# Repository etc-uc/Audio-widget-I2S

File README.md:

# Audio-widget-I2S
**Interfata audio USB utilizand un AVR32 pe protocolul I2S**

## Introducere
>
>Inca din timpurile dinaintea erei digitale, consumatorii de audio **asa zisii audiofili** au fost in cautare de metode pentru reducerea la minim a distorsiunilor transmise catre difuzoare,si implicit,percepute de urechea umana.In vremea respectiva,data fiind si complexitatea destul de redusa a dispozitivelor,ideea reducerii distorsiunilor in sisteme era destul de limitata de topologiile propuse,de aceea aparitia sistemelor digitale de procesare in audio a dus la reducerea drastica a neajunsurilor semnalelor analogice.Pentru **puristi** , circuitele digitale si DSP-urile sunt considerate _un sacrilegiu_ adus audiofiliei,dar este unul justificat,deoarece in ciuda complexitatii mai ridicate fata de un circuit analog pur , sistemele digitale sunt mult mai eficiente fata de complementele sale,iar posibilitatea customizarii lor este foarte mare (spre deosebire de un circuit analogic unde,pentru a modifica o caracteristica trebuie regandit tot circuitul,in cazul unui circuit digital cu uC este doar o problema de software).

>Aparitia interfetelor audio s-a facut odata cu dezvoltarea PC-urilor si inregistrarea de muzica/sunete pe medii digitale , in pofida benzilor magnetice si a discurilor de vinil , deoarece era necesara o metoda de redare a sunetelor stocate pe calculatoarele vremii. De altfel,primele asa zise **placi de sunet** si-au facut aparitia prin calculatoare in jurul generatiei 80486 , cand deja exista o oarecare structura de operare stabila pe 16 biti , iar pentru o esantionare simpla a sunetelor erau arhisuficiente instructiunile implementate de Intel in procesoarele respective.
>>_Daca facem referinta la vremurile actuale,se poate spune ca practic nici nu se punea problema de calitate sau termenul de **Hi-Fi** in acele vremuri,dar acele sunete au reprezentat ceea ce urma sa fie boom-ul erei digitale_
>
>Ca si istorie a acestei ere in care traim,se pot scrie foarte multe lucruri deja cunoscute,asa ca voi incerca sa ma concentrez pe esential.

>Ideea de "calitate audio" pe digital a aparut in momentul lansarii pe piata mondiala a CD-ului (acel lucru care acum multora dintre noi ni se pare atat de outdated,ori chiar nu il mai folosim),dar el a avut cea mai mare influenta in aparitia de tehnologii de compresie si codare audio.Ca si concept,ideea de CD a aparut prin anul 1980 ,cand Philips si Sony au incheiat un parteneriat de cercetare in domeniul digital,dorindu-se un mediu de stocare unic transmisibil,care sa aibe un spatiu de stocare a informatiilor mult mai mare decat cel al dischetelor "floppy" si al benzilor magnetice,dar totusi sa nu coste cat un hard disk al vremurilor (memo: un hard disk de tip Winchester avea o capacitate de maxim 128MB , cantarea in jur de 15-20kg si era cam cat un desktop SFF actual ca dimensiuni si costa in jur de ~5.000 de dolari unul?).
>>Standardul CD a fost definitivat in jurul anului 1983,iar in urma intelegerii realizate intre cele 2 concerne se va realiza trecerea industriei audio catre acest mediu.

>Se pune problema "compresiei audio".In a nutshell,algoritmul de compresie audio se refera la un standard de scriere-redare a sunetelor pe calculatoare. Calculatoarele,la momentul respectiv avand sisteme de operare stabile precum UNIX si DOS (vorbind de anii '80,dar regula se aplica si in prezent pe sistemele actuale),pentru a reda sunetele stocate pe medii precum hard-diskul se folosesc de niste software numite **codec** .
>>Codecurile,in esenta,sunt niste pseudo-drivere pe care sistemul de operare le interpreteaza atunci cand se executa in sistem un fisier cu extensia ce corespunde codecului respectiv.
>>Adica,spre exemplu, avem un fisier cu extensia ".mp3" , SO va sti ca la instantierea acestui fisier va trebui sa apeleze un Codec LAME(Lame Ain't an MP3 Encoder - care este o derivatie imbunatatita de-a lungul anilor de diversi programatori din conceptul original gandit de institutul Fraunhofer din Germania).

>De altfel , toate procedeele de redare/compresie si extensiile de sistem au fost posibile datorita codarii PCM (Pulse Code Modulation).
PCM reprezinta transformarea semnalelor analogice in semnale digitale printr-un algoritm de esantionare constanta a amplitudinii semnalului analogic ,iar fiecare esantion este cuantizat la cea mai apropiata valoare dintr-o gama de cuante apropiate.
>>**Codarea PCM prezinta 2 proprietati ce determina calitatea conversiei semnalului original raportat la acesta : rata de esantionare a semnalului si _bit depth_,care reprezinta cantitatea de biti al fiecarui esantion realizat (un CD-Audio prezinta un bit depth de 16 biti per esantion , pe cand un Blu-ray sau DVD-Audio 24 de biti per esantion).**
>>> Extensiile posibile unei compresii PCM sunt ".wav" ,".L16",".PCM",".AIFF",".AU"

>Pe baza codarii/compresiei PCM a fisierelor audio, cei de la Philips au realizat in anul 1986 (si ulterior revizuit in 1996) un protocol de transmisie seriala al datelor audio intre dispozitive / circuite integrate , protocol care inca se foloseste cu succes si in prezent in dispozitivele audio. Este cunoscut sub acronimul I2S sau IIS **Inter-IC Sound** si se bazeaza pe o magistrala sincrona de transmisie de date (clockul de transmisie intre circuite este separat de magistrala de date,deci implicit receptorul nu mai are nevoie de un circuit suplimentar de refacere a frontului de ceas trimis de emitator).
>Protocolul este relativ usor de interpretat, in principal avem de-a face cu 3 semnale : bit clock line(**BCLK**) , word clock line (cunoscut sub denumirea oficiala de 'word select' **WS** sau 'left-right clock' **LRCLK** ) si cel putin o linie de date multiplexata **SD**

>>Adeseori se mai poate intalni peste cele 3 semnale cunoscute inca un semnal de tact (care nu face parte din protocol) cu rolul de a sincroniza operatiile interne ale DAC-urilor cu cele ale controllerului . Este gasit sub acronimul de "Master clock" **MCLK**
>>>Frecventa tipica de lucru se calculeaza dupa formula : **MCLK = 256 * LRCLK**

###### Cum functioneaza protocolul:

>Semnalul de "Word Select" permite dispozitivului receptor sa 'vada' ce canal urmeaza sa fie trimis , deoarece I2S permite ca pe aceeasi linie de date sa fie trimise 2 canale,fiind un semnal cu factor de umplere 50% si frecventa egala cu cea de esantionare a semnalului trimis.
>>**Pentru semnale stereo , in brosura de specificatii a I2S se spune ca semnalul audio de pe canalul stang se transmite pe palierul de 0 al Word Select , iar canalul drept pe palierul de 1 . De obicei , semnalul "Word Select" este sincronizat dupa fronturile cazatoare ale semnalului BCLK , deoarece datele sunt zavorate pe fronturile crescatoare**.
>>
>Se stabileste semnul liniei de date si se codeaza in complement fata de 2 cu primul bit MSB-ul . **Acest lucru permite ca numarul de biti per cadru sa fie arbitrar , fara a fi nevoie de "negociere" intre emitator si receptor **.

## Specificatii montaj:

1.
 a)Microcontroller utilizat:  Atmel AT32UC3A3256 
 >>>  A complete system-on-chip 32-bit AVR microcontroller. It is designed for cost-sensitive embedded applications that require low power consumption, high code density and high performance.

 >>> The microcontroller's Memory Protection Unit (MPU) and fast, flexible interrupt controller support the latest real-time operating systems. Higher computation capabilities are achievable using a rich set of DSP instructions. The device incorporates on-chip flash and SRAM memories for secure and fast access. 64 KBytes of SRAM are directly coupled to the 32-bit AVR UC3 for performance optimization. Two blocks of 32 Kbytes SRAM are independently attached to the high speed bus matrix for real ping-pong management.

 >>> The microcontroller achieves exceptionally high data throughput by combining the multi-layered 32-bit AVR databus,128 KB on-chip SRAM with triple high speed interfaces, multi-channel peripheral, memory-to-memory DMA controller, high-speed USB embedded host, SD/SDIO card, MLC NAND flash with ECC, and SDRAM interfaces.

 >>> This device features 256KB internal high-speed flash and full-duplex multi-channel I2S audio interface.
 
 b) DAC utilizat: PCM5102A

 >>>The PCM510xA devices are a family of monolithic CMOS-integrated circuits that include a stereo digital-to-analog converter and additional support circuitry in a small TSSOP package. The PCM510xA devices use the latest generation of TI’s advanced segment-DAC architecture to achieve excellent dynamic performance and improved tolerance to clock jitter.

 c) Amplificator/buffer iesire folosit : TPA6120
 >>>In applications requiring a high-power output, very high fidelity headphone amplifier, the TPA6120A2 replaces a costly discrete design and allows music, not the amplifier, to be heard. The TPA6120A2’s current-feedback AB amplifier architecture delivers high bandwidth, extremely low noise, and up to 128dB of dynamic range.
 
2.Utilizeaza USB Audio Class 1 / 2.

3.Capabilitati de redare audio pana la 24bit/96kHz (bit depth / sampling rate).

4.Tensiune de alimentare: 5V (doar daca utilizam DAC-ul si interfata I2S) , +12/-12V (daca se utilizeaza si amplificatorul final)

5.Consum max: 1-1,5A (este necesara alimentare suplimentara deoarece amplificatorul final de casti se alimenteaza diferential) 

### Constructie montaj:

Contructia se bazeaza pe un design modular , iar in acest sens voi concepe intregul sistem pe 4 placi:
 - una o va constitui interfata emulatoare usb-i2s
 - o placa pentru DAC si , eventual , buffere de iesire
 - o placa pentru amplificatorul final
 - o placa pentru alimentare suplimentara

Ideea conceperii montajului intr-un sistem modular este pentru imbunatatirea "lantului" pe decursul timpului (ex. realizarea unui DAC mai performant din perspectiva SNR / PSRR sau schimbarea unei surse liniare cu una in comutatie sau adaugarea de acumulatori pentru portabilitate etc.)

De altfel,un montaj modular poate presupune o asezare mai buna in cutie si,totodata, un ecranaj mai bun al partilor **mai sensibile** fata de circuitul de alimentare.

#### Particularitate software:

Ideea interfetei I2S este bazata pe un proiect deja existent in mediul online , anume SDR-Widget https://github.com/borgestrand/sdr-widget

Asadar hardware-ul din spatele acestui sistem a fost dezvoltat in asa fel incat firmware-ul cu care am programat AVR-ul sa fie direct compatibil.
Din punct de vedere functional, din software-ul dezvoltat in acel proiect am folosit doar mediul de comunicare audio via USB (UAC1 si UAC2) si partea de control software a volumului.

Consider ca nu este necesar sa uploadez toate sursele C pentru generarea firmware-ului , asa ca voi atasa fisierul HEX(.elf) continand versiunea stabila de firmware pentru acest sistem.

#### Programarea microcontrollerului:

Seria UC3A3 de la Atmel(Microchip-ish or whatsoever) au incarcate din fabricatie un bootloader ce contine un USB DFU(Device Firmware Upgrade).
DFU este un protocol ce se regaseste in orice tip de terminal ce are propriul sistem de operare,deoarece faciliteaza operatiunea de rescriere a software-ului deja setat in terminalul respectiv utilizand o interfata de comunicare uzuala.

De aceea , microcontrolerul pe care l-am utilizat in montaj (AT32UC3A3256) l-am programat cu doar un USB si programul ATMEL FLIP 3.4.7 , utilizand din acesta batchisp-ul (pentru ca,prin constructia sa , programul Flip nu suporta la un nivel stabil aceasta serie de uC-uri).

Nu mai pot reproduce inca o data procesul de programare (sau il voi mai face ulterior daca dezvolt un alt firmware mai performant pentru cerinta data), dar comanda de programare pe care am utilizat-o este:
**batchisp -device at32uc3a3256 -hardware usb -operation erase f memory flash blankcheck loadbuffer widget.elf program verify start reset 0**
Unde widget.elf se inlocuieste cu denumirea HEX-ului de urcat pe uC.

Dupa introducerea comenzii se executa programarea uC-ului in 11 pasi:

AT32UC3A3256 - USB - USB/DFU

Device selection....................... PASS

Hardware selection..................... PASS

Opening port........................... PASS

Reading Bootloader version............. PASS    1.0.3

Erasing................................ PASS

Selecting FLASH........................ PASS

Blank checking......................... PASS    0x00000 0x3ffff

Parsing ELF file....................... PASS    widget.elf

WARNING: The user program and the bootloader overlap!

Programming memory..................... PASS    0x00000 0x1c43f

Verifying memory....................... PASS    0x00000 0x1c43f

Starting Application................... PASS    RESET   0

Summary:  Total 11   Passed 11   Failed 0

Dupa programarea uC-ului calculatorul "teoretic" ar trebui sa il recunoasca automat si sa instantieze driverul necesar utilizarii acestuia. Cel putin in Windows 10 nu exista probleme de compatibilitate a driverelor, recunoscandu-le automat la conectarea interfetei. Posibil sa existe probleme de "backwards compatibility" a firmware-ului cu versiunile mai vechi de Windows,dar se rezolva instaland manual "inf drivers".

## Utilizare:

Ca si software , interfata este gandita destul de simplist,deoarece se considera ca este suficient doar un control al volumului,niciun fel de egalizare grafica sau corectie de tonuri.
Software-ul de control este scris pe framework-ul ASIO (_Audio Stream Input-Output_).
Ca si un mic memo : ASIO este un protocol de drivere open-sourced pentru "sound card-uri" specificat in industria audio de firma Steinberg.
Ca si functionare a protocolului : ASIO produce un bypass al caii audio normale la nivel de aplicatie din sistemul de operare utilizat,astfel incat sa se evite "layer-ele" suplimentare la nivel de software.Acest lucru permite aplicatiei sa se conecteze la sound card direct,fara intermedierea sistemului de operare in procesul respectiv.Acest lucru duce la o reducere foarte mare a latentei de transfer a informatiei audio de la soft la hard.

>>Foobar2000 **logo de mai sus** este un player audio freeware (nu este necesara licenta de utilizare) pentru Microsoft Windows, iOS, si Android dezvoltat de Peter Pawłowski.Ca si software este cunoscut designul sau extrem de modular , multitudinea de caracteristici si flexibilitatea in configurare pentru user.
>>Acest player suporta foarte multe formaturi audio , prezinta o multitudine de caracteristici organizarea fisierelor , metadata si are implementata o interfata de convertor utilizabila in linie de comanda (transcodare fisiere si ripping CD-Audio). 

In poza , aplicatia redand un fisier audio .FLAC (lossless audio codec) , configurat pentru output pe WASAPI* , buffer length minim pentru jitter scazut intre interfata de comunicare si controller.

>>>> **Ca si ASIO , WASAPI (Windows Audio Session API) este un plugin utilizat in audio pentru a permite trecerea fluxului de date audio direct intre terminalul audio din aplicatia ce reda fisierele audio**
>>>> Diferenta principala dintre ASIO si WASAPI este ca , primul este un plugin open-source (poate fi luat si modificat in drivere de oricine) , pe cand cel din urma este conceput de MICROSOFT si na...copyright in a nutshell daca vrea cineva sa modifice core-ul plugin-ului.

>>>Ca si comparatie intre cele 2 pluginuri, ambele sunt foarte usor de utilizat si instalat , cu precizarea ca ASIO functioneaza cu doar cu dispozitivele ce au descriptori dedicati in driverele lor , pe cand WASAPI functioneaza cu orice fel de endpoint device , atata timp cat este selectat pluginul ca si output pentru device-ul respectiv si nu adresa "Direct Sound".

>>>> **De precizat ar mai fi ca,atata timp cat un eveniment WASAPI / ASIO este executat , nu se mai reda niciun flow audio din partea altor aplicatii pana nu se incheie evenimentul respectiv**

### Ansamblare

Pentru incapsularea proiectului am ales sa separ sursa de alimentare de partea de DAC+Amplif casca pentru a evita producerea de zgomot inutil in sistem. **ideea este tocmai de a avea un zgomot minim in tot lantul si atunci este de preferat ca sursa sa stea cat mai departe de elementele sensibile ale sistemului**

Asadar , pentru incapsularea amplificatorului am comandat o carcasa din aluminiu eloxat argintiu de la Hammond,cu dimensiunile 220x103x31mm (LxlxH) , iar pentru sursa probabil voi utiliza o cutie de ramificatie electrica **de aparataj** pentru ca nu are prea mare importanta aspectul ei (ca oricare alta sursa de alimentare, va sta intr-un loc prea putin vizibil).

Pentru alimentare voi monta pe ambele carcase o mufa DIN 3P ce se asigura cu o piulita de blocare , cu 3 pini deoarece amplificatorul se alimenteaza diferential.

#### Masuri pentru evitarea producerii/captarii de zgomot in circuit:

1.Decuplarea alimentarilor cu condensatoare de valoare foarte mica (capabilitate de lucru in frecvente mari) - zeci/sute nF si de valoare f. mare (capabilitate de lucru in frcvente mici).

2.Torsadarea cablurilor de alimentare din carcasa (reducerea emisiilor em. in circuit).

3.Separarea pe cat posibil a circuitelor de semnal mic fata de cele de alimentare.

4.Utilizarea unui punct comun de legatura a maselor din intregul circuit (star pattern sau line pattern , in cazul meu voi utiliza un line pattern deoarece nu sunt implicati curenti mari de circuit - max 1A peak).

5.Utilizare de filtraj cat mai generos - capacitatile mari de filtrare implica un riplu foarte mic al sursei de alimentare,deci posibilitatea aparitiei unui zgomot perturbator pe alimentare minim.
>>Cu riscul aparitiei unui curent de incarcare foarte mare,se recomanda utilizarea de capacitati mari pentru evitarea riplului,mai ales in circuite unde este nevoie de curenti mari pe perioade scurte.
>>>Problema curentilor mari de incarcare se rezolva cu niste rezistente serie cu condensatorii (zeci de ohmi),care sa limiteze curentul prin ei la pornire,dupa aceea rezistentele se sunteaza cu un releu si se utilizeaza normal **soft-start empiric**

**RIPLU -> componenta alternativa aparuta la ciclurile de incarcare-descarcare ale condensatorilor intr-un redresor**

## Limitari si probleme aparute de-a lungul constructiei:

Cea mai mare problema am avut-o la ansamblare...un cosmar si jumatate din perspectiva unei persoane ce a lucrat mai tot timpul cu componente THT si acum s-a lovit de "zidul" lipirii de componente SMD. Am facut si prostia de a ma apuca si fix de cea mai complicata placa mai intai , cea a interfetei USB-I2S, cei 144 de pini ai uC-ului mi-au dat de furca pana l-am lipit cum trebuie,deoarece m-am incapatanat sa il lipesc pin cu pin cu letconul si la un moment dat aveam efectiv mai multe scurturi intre pini decat pini lipiti cum trebuie de placa.Dar acest mic detaliu a fost rezolvat cu mult flux,efect capilar si injuraturi cand nu voia fludorul sa plece dintre pini pe talpa varfului folosit.
De altfel ,toate componentele 0603 de pe aceasta placa mi-au provocat o mare placere de a invoca sfinti de-a lungul lipirii lor.
Apexul a fost atins la ora 3 noaptea,dupa ce am terminat de lipit placuta interfetei,am legat-o la USB si am realizat,cu stupoare,ca nu face nimic...nu se conecta la calculator.Din nou,nervi injuraturi,abtineri din a tranti minunea peste tot.
A doua zi am rezolvat problema in 10 minute : stabilizatorul 5V-3.3V de pe placa avea un pin " in aer " si nu aveam output pentru alimentarea uC-ului.

**Morala ar fi ca: prea multe beri si oboseala dupa 12 ore de alergat dintr-o parte in alta dauneaza bunei atentii asupra realizarii unui montaj.**

Montarea placii DAC a fost pretty straightforward , nu am intampinat cine stie ce dificultati, mai ales acum avand experienta lipirii "ghindoacelor" 0603 pe placa interfetei ... componentele 1206 si integratul SSOP cu 20 de pini au fost PARFUM!!

Placa amplificatorului am montat-o si cam atat, pana acum m-am folosit doar de mufa de casca pentru a vedea daca functioneaza dacul cum trebuie.Urmeaza sa montez si sursa de alimentare si o voi testa si pe aceasta.

Singura limitare "constructiva" mi-am creat-o singur,din pricina carcasei alese pentru circuit. Am ales o carcasa cu inaltimea de 31mm, insuficient pentru inaltimea potentiometrului pe PCB-ul amplificatorului.Am fAacut aceasta eroare deoarece nu am tinut cont ca primele caneluri de suport pentru cablaje incep de la aproximativ 5mm fata de fundul carcasei , ceea ce ar insemna ca depasesc inaltimea montarii capacului cu potentiometrul cu vreo 2mm din ce am masurat.

Solutia: montat potentiometrul si mufa de casca solitare pe panoul frontal si facut legaturi cu PCB-ul prin cabluri torsadate si mufate.

## Constructie sursa de alimentare

Cel mai mare semn de intrebare posibil din tot proiectul ce se putea pune : Ce sursa de alimentare sa folosesc , liniar sau comutatie? Cum naiba fac sa nu stric tot "zenul" montajului cu zgomote inutile aduse de catre o sursa?

De altfel, orice sursa as alege inevitabil tot ma aleg cu un oarecare zgomot in circuit,pentru ca nu poti elimina o cauza fara a genera un alt defect.

Solutia : **in mintea mea** 

Se da o sursa clasica stabilizata , realizata extern circuitelor de semnal / amplificat. Sursa o voi realiza cu un transformator incapsulat in rasina de 10-15VA,deoarece nu am nevoie de foarte multa putere de iesire. Redresare cu punte de diode clasise / schottky (inca nu m-am decis daca se merita efortul pentru diode schottky,mai ales pentru frecventa retelei).

Filtraj inainte de stabilizare 2x4700uF + decuplarile de rigoare pe diode cu 100nF + 220-470nF in bratul stabilizatorului + buffer suplimentar de curent dupa stabilizatoare 2x4700uF + 100nF. Bufferul il voi amplasa in carcasa interfetei,pentru a realiza si punctul comun de legatura al masei pentru tot circuitul.

Imi asum riscul ca voi avea un curent initial de incarcare enorm pentru acel transformator (10000uF insumati pot produce un oarecare deranj mai ales pentru o sursa ce nu debiteaza un curent foarte mare),dar acest lucru il voi vedea exact cand voi finaliza si acest pas.

Stabilizatoarele probabil vor fi clasicele 7812/7912 (not so many fancy things there , sursa trebuie sa fie cat mai simpla si eficienta,fara prea multe briz-briz-uri).

## Final updates

1. La indemnul tatalui meu am achizitionat inca o carcasa de la Hammond , "sora" celei pe care am prezentat-o mai sus , din pricina incapsularii tuturor modulelor intr-un singur loc si nu "in o mie si una de cutiute". Ca si forma sunt identice,singura diferenta o face inaltimea lor (31mm vs 53mm).

2. Am ansamblat sursa de alimentare *dupa lupte seculare as putea spune* si am descoperit ca pentru ce am eu nevoie 4700uF pe brat de alimentare este mai mult decat suficient.Dupa cum ma asteptam , folosind pattern-ul line pentru legarea maselor la comun si decuplarea "sanatoasa" a elementelor sursa nu induce zgomot in circuite...great succes i would say :)
Singura problema: am facut-o pe cablaj de test pentru ca nu am mai avut rabdare sa corodez o foaie de cablaj ... but not so much of a thing pentru ca am tinut cont de dimensionarea corecta a traseelor de circuit si pozitionarea elementelor disipatoare de caldura astfel incat circuitul sa nu se degradeze rapid,dar totusi sa fie compact si sa se incadreze in aria necesara.

3. Odata cu sursa,am testat intr-un final si amplificatorul final si pot spune ca a meritat asteptarea...chiar suna foarte bine in combinatie cu dacul facut.Imi era foarte teama de imperecherea lor,dar a fost doar paranoia si atat.

Dar credeti ca am scapat de peripetii? Nicio sansa, la prima "cheie" amplificatorul nu a vrut sa cante nici sa-l fi batut.
Am incercat sa elimin toate posibilele cauze , in prima instanta am inlocuit toate cablurile de legatura dar degeaba ca tot nu a vrut sa mearga. Am sucit sursa pe toate partile,am zis ca poate am legat ceva prost pe acolo,dar nicio sansa,toate legaturile erau facute bine si aveam tensiune aproape egala pe ambele brate de alimentare.Ce mama masii sa mai aiba si placa asta acum?!
Am legat dacul direct la iesirea de casti si aveam semnal redat,deci nicio sansa sa fie din alta parte problema.
Deschid schema , stau si ma uit la layoutul cablajului si dupa realizez ca integratul meu amplificator este montat invers pe pcb ... #$%^#$$@$^$%^#$#@%#$^ masii de treaba. Tuff job de dezlipit din cauza fludorului ce tine padul de disipatie termica lipit de cablaj.Din nou,sfinti,altare si tot tacamul pana l-am dezlipit si relipit (noroc cu colegul de camera muuuultt mai rabdator decat mine).
Dupa ce l-am relipit zeii siliciului au decis sa nu imi arda integratul si l-am putut auzi cantand, finally . Intr-un final , tot lantul meu audio este gata si functional, iar singurul lucru ce mi-a mai ramas de facut este sa gauresc panoul frontal si sa strang ultimele 4 suruburi de pe cutie :)

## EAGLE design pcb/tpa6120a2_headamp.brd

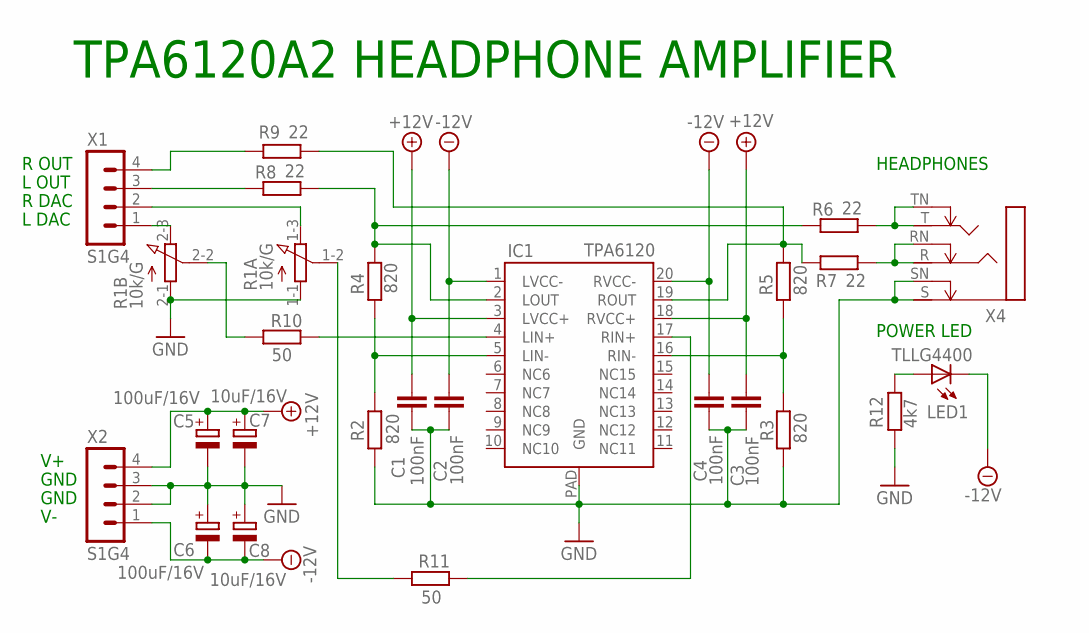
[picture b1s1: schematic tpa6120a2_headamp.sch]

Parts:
C1, C2, C3, C4: 100nF; C1206
C5, C6: 100uF/16V; SMC_D
C7, C8: 10uF/16V; SMC_C
IC1: TPA6120; SO20POWERPAD
LED1: TLLG4400; LED3MM
R1: 10k/G; ALPS-RK27-DUAL
R2, R3, R4, R5: 820; R1206
R6, R7, R8, R9: 22; R1206
R10, R11: 50; R1206
R12: 4k7; R1206
X1, X2: S1G4; MA04-1
X4: NMJ6HCD2

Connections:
+12V: C1.1, C3.1, C5.+, C7.+, IC1.3 (LVCC+), IC1.18 (RVCC+), X2.4
-12V: C2.1, C4.1, C6.-, C8.-, IC1.1 (LVCC-), IC1.20 (RVCC-), LED1.K (C), X2.1
GND: C1.2, C2.2, C3.2, C4.2, C5.-, C6.+, C7.-, C8.+, IC1.PAD (GND), R1.1-1 (1), R1.2-1 (1), R2.1, R3.1, R12.1, X2.2, X2.3, X4.S, X4.SN
unnamed: IC1.19 (ROUT), R5.2, R7.1, R9.2
unnamed: IC1.5 (LIN-), R2.2, R4.1
unnamed: IC1.16 (RIN-), R3.2, R5.1
unnamed: IC1.2 (LOUT), R4.2, R6.1, R8.2
unnamed: R6.2, X4.T, X4.TN
unnamed: R1.2-3 (3), X1.1
unnamed: R1.1-3 (3), X1.2
unnamed: R1.2-2 (2), R10.1
unnamed: R1.1-2 (2), R11.1
unnamed: R7.2, X4.R, X4.RN
unnamed: IC1.4 (LIN+), R10.2
unnamed: IC1.17 (RIN+), R11.2
unnamed: LED1.A, R12.2
unnamed: R8.1, X1.3
unnamed: R9.1, X1.4

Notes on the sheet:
TPA6120A2 HEADPHONE AMPLIFIER
L DAC
R DAC
L OUT
R OUT
GND
HEADPHONES
POWER LED

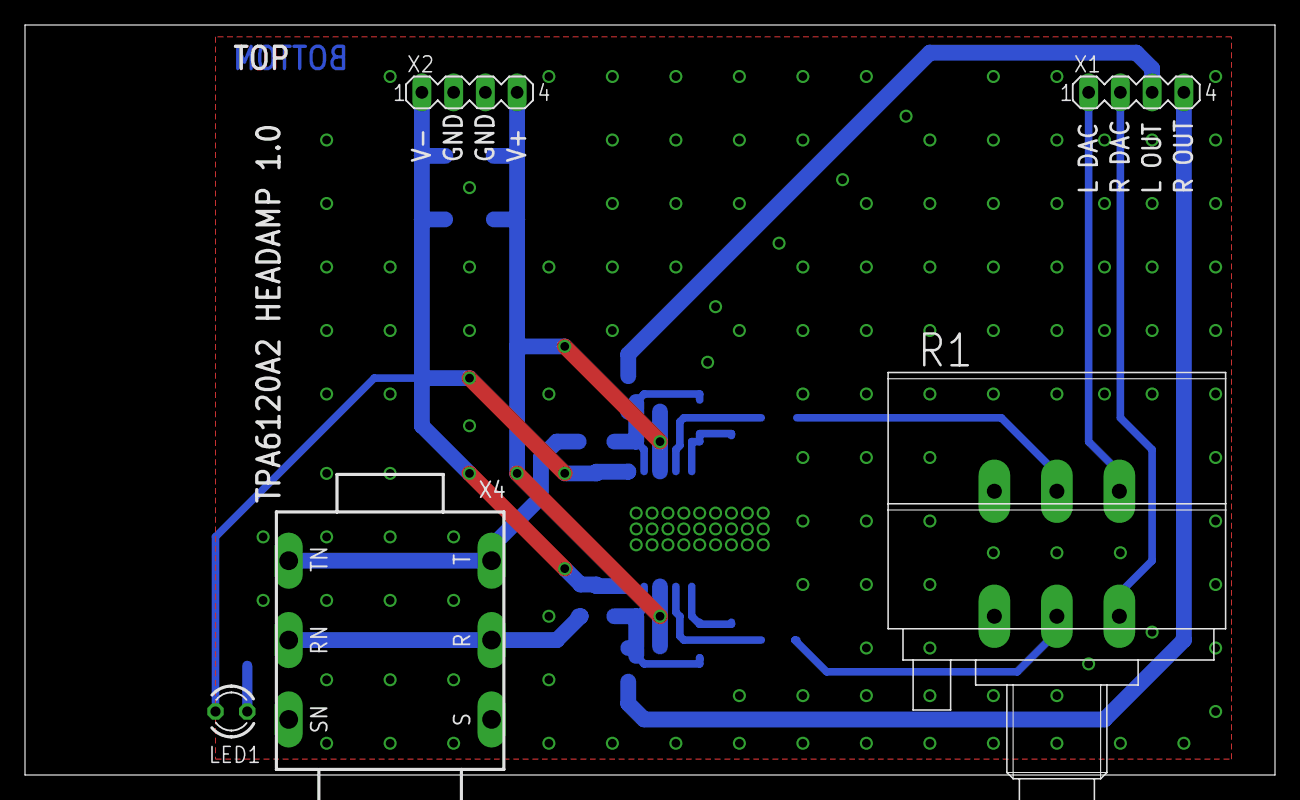
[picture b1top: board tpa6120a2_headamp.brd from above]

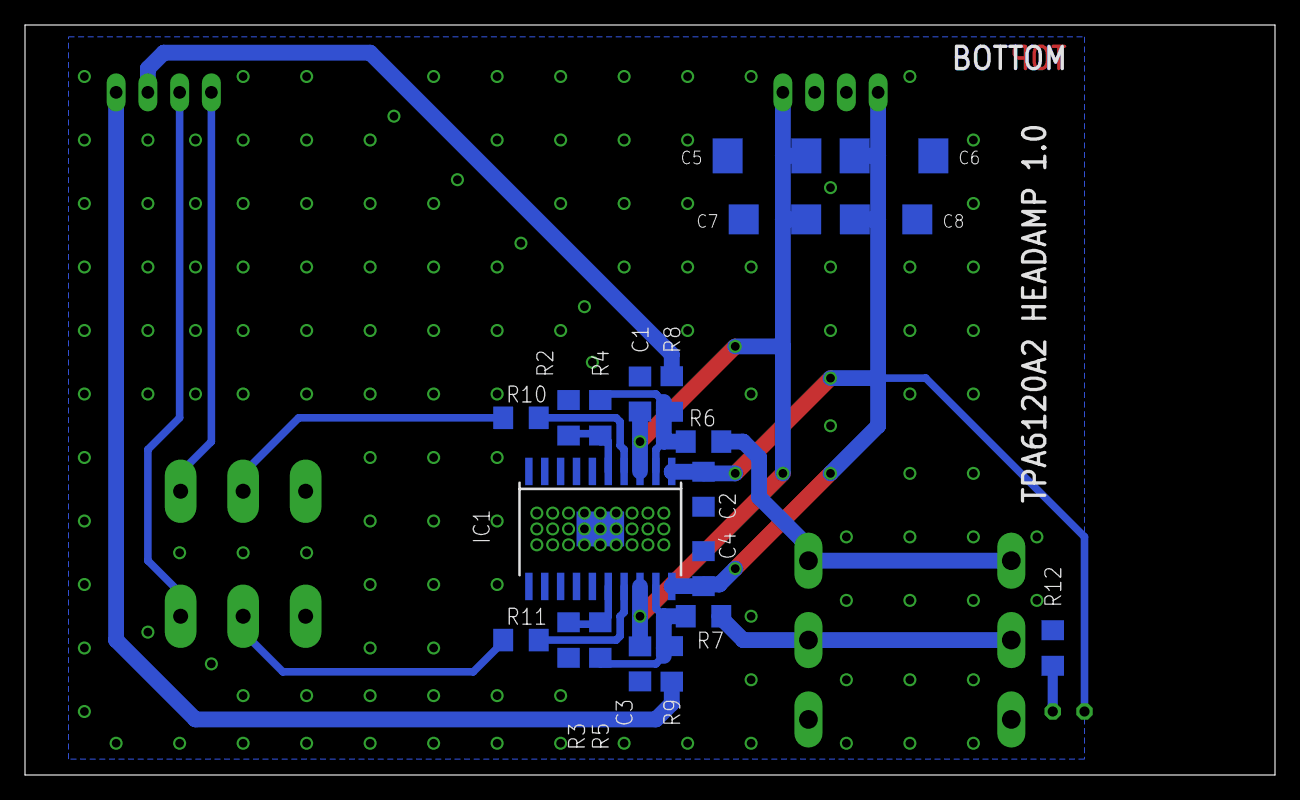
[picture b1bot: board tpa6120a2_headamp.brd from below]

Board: 2 copper layers, 100.0 x 60.0 mm, 25 parts (20 on the bottom side), 18 nets.

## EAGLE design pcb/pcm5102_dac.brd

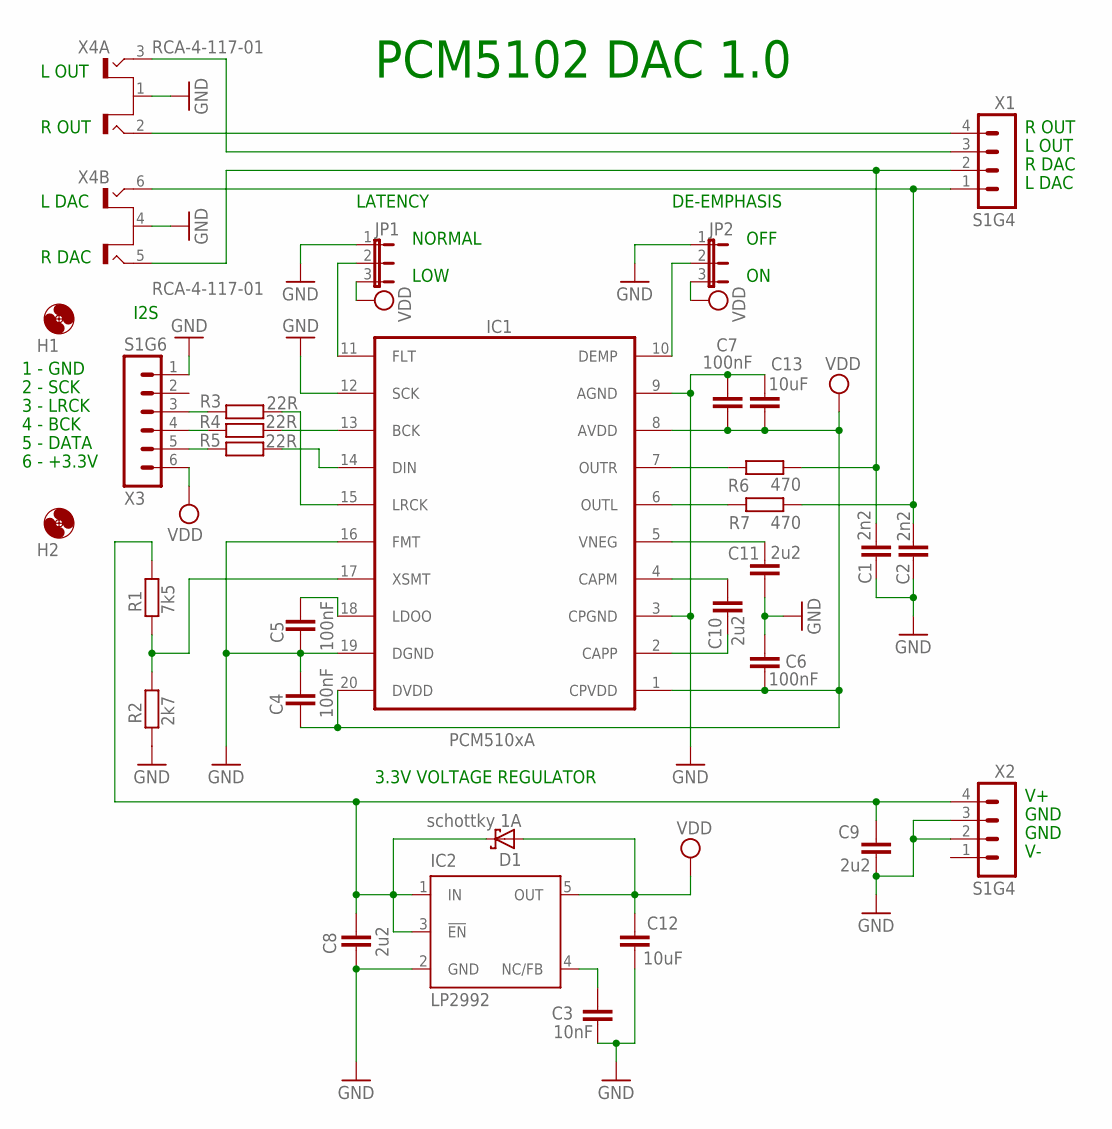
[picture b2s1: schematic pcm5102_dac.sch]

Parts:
C1, C2: 2n2; C1206
C3: 10nF; C1812
C4, C5, C6, C7: 100nF; C1206
C8, C9, C10, C11: 2u2; C1206
C12, C13: 10uF; C1206
D1: schottky 1A; SMB
H1, H2: MOUNT-HOLE3.2; 3,2
IC1: PCM510xA; TSSOP20
IC2: LP2992; SOT23-DBV
JP1, JP2: DIL; JP2
R1: 7k5; R1206
R2: 2k7; R1206
R3, R4, R5: 22R; R1206
R6, R7: 470; R1206
X1, X2: S1G4; MA04-1
X3: S1G6; MA06-1
X4: RCA-4-117-01

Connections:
GND: C1.2, C2.2, C3.2, C4.1, C5.2, C6.1, C7.1, C8.2, C9.2, C11.2, C12.2, C13.1, IC1.3 (CPGND), IC1.9 (AGND), IC1.12 (SCK), IC1.16 (FMT), IC1.19 (DGND), IC2.2 (GND), JP1.1, JP2.1, R2.1, X2.2, X2.3, X3.1, X4.1 (S), X4.4 (S)
LDOO: C5.1, IC1.18 (LDOO)
unnamed: R5.1, X3.5
unnamed: C8.1, C9.1, D1.C, IC2.1 (IN), IC2.3 (!EN), R1.2, X2.4
unnamed: X1.3, X4.3 (T2)
unnamed: C3.1, IC2.4 (NC/FB)
unnamed: IC1.17 (XSMT), R1.1, R2.2
unnamed: X1.4, X4.2 (T1)
unnamed: C2.1, R7.2, X1.1, X4.6 (T2)
unnamed: R3.1, X3.3
unnamed: R4.1, X3.4
unnamed: IC1.13 (BCK), R4.2
unnamed: IC1.14 (DIN), R5.2
unnamed: IC1.11 (FLT), JP1.2
unnamed: IC1.10 (DEMP), JP2.2
unnamed: IC1.15 (LRCK), R3.2
unnamed: C10.1, IC1.4 (CAPM)
unnamed: C10.2, IC1.2 (CAPP)
unnamed: C11.1, IC1.5 (VNEG)
unnamed: IC1.7 (OUTR), R6.1
unnamed: IC1.6 (OUTL), R7.1
unnamed: C1.1, R6.2, X1.2, X4.5 (T1)
VDD: C4.2, C6.2, C7.2, C12.1, C13.2, D1.A, IC1.1 (CPVDD), IC1.8 (AVDD), IC1.20 (DVDD), IC2.5 (OUT), JP1.3, JP2.3, X3.6

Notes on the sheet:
1 - GND
2 - SCK
3 - LRCK
4 - BCK
5 - DATA
6 - +3.3V
I2S
PCM5102 DAC 1.0
R OUT
L OUT
R DAC
L DAC
GND
NORMAL
LOW
DE-EMPHASIS
LATENCY
OFF
3.3V VOLTAGE REGULATOR

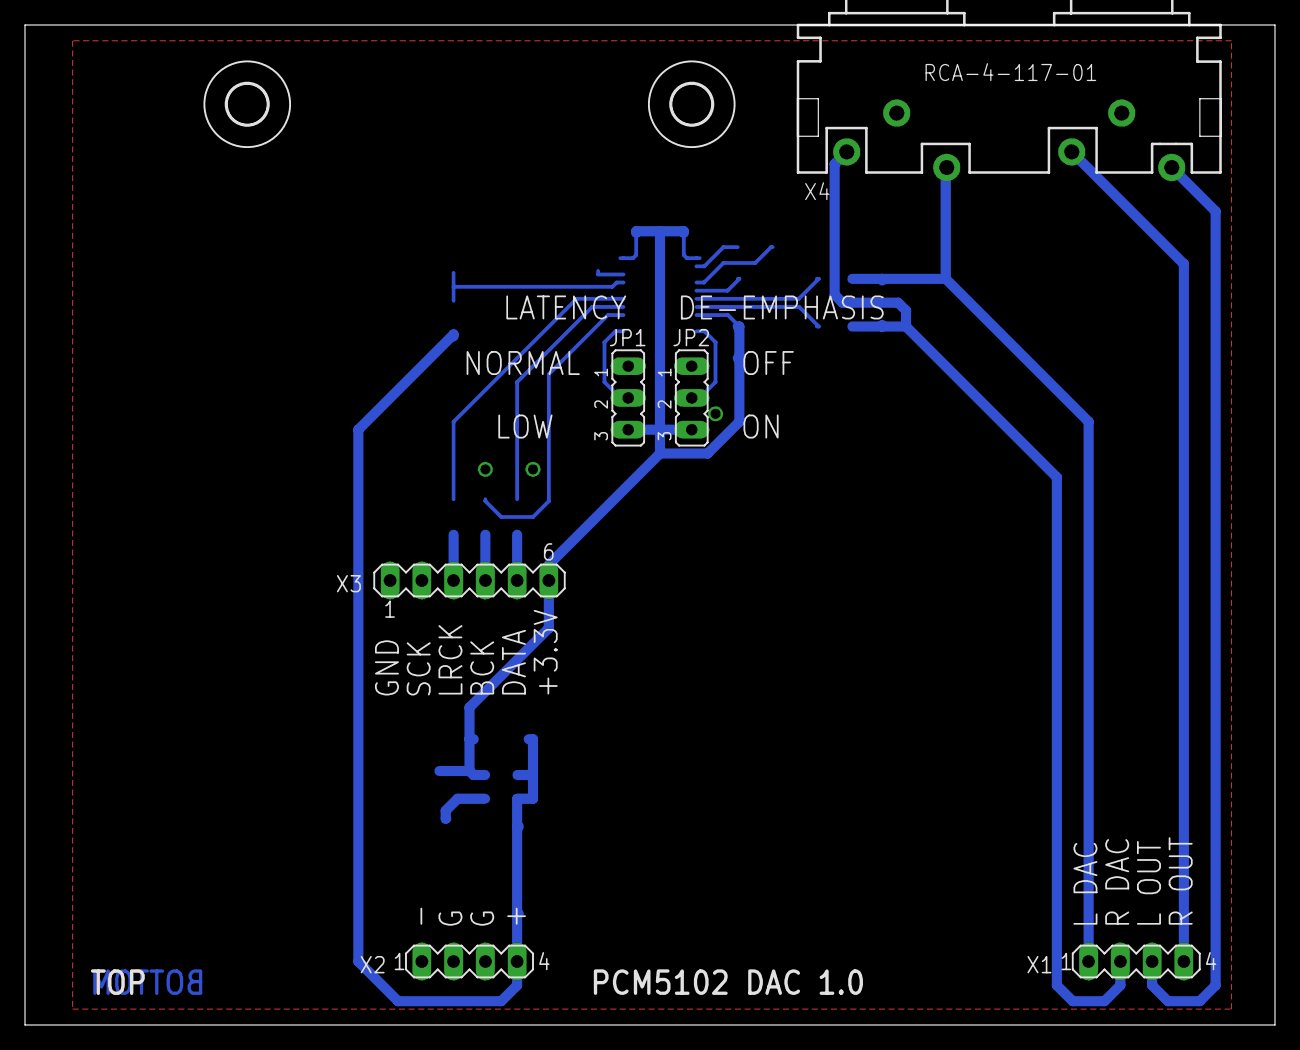
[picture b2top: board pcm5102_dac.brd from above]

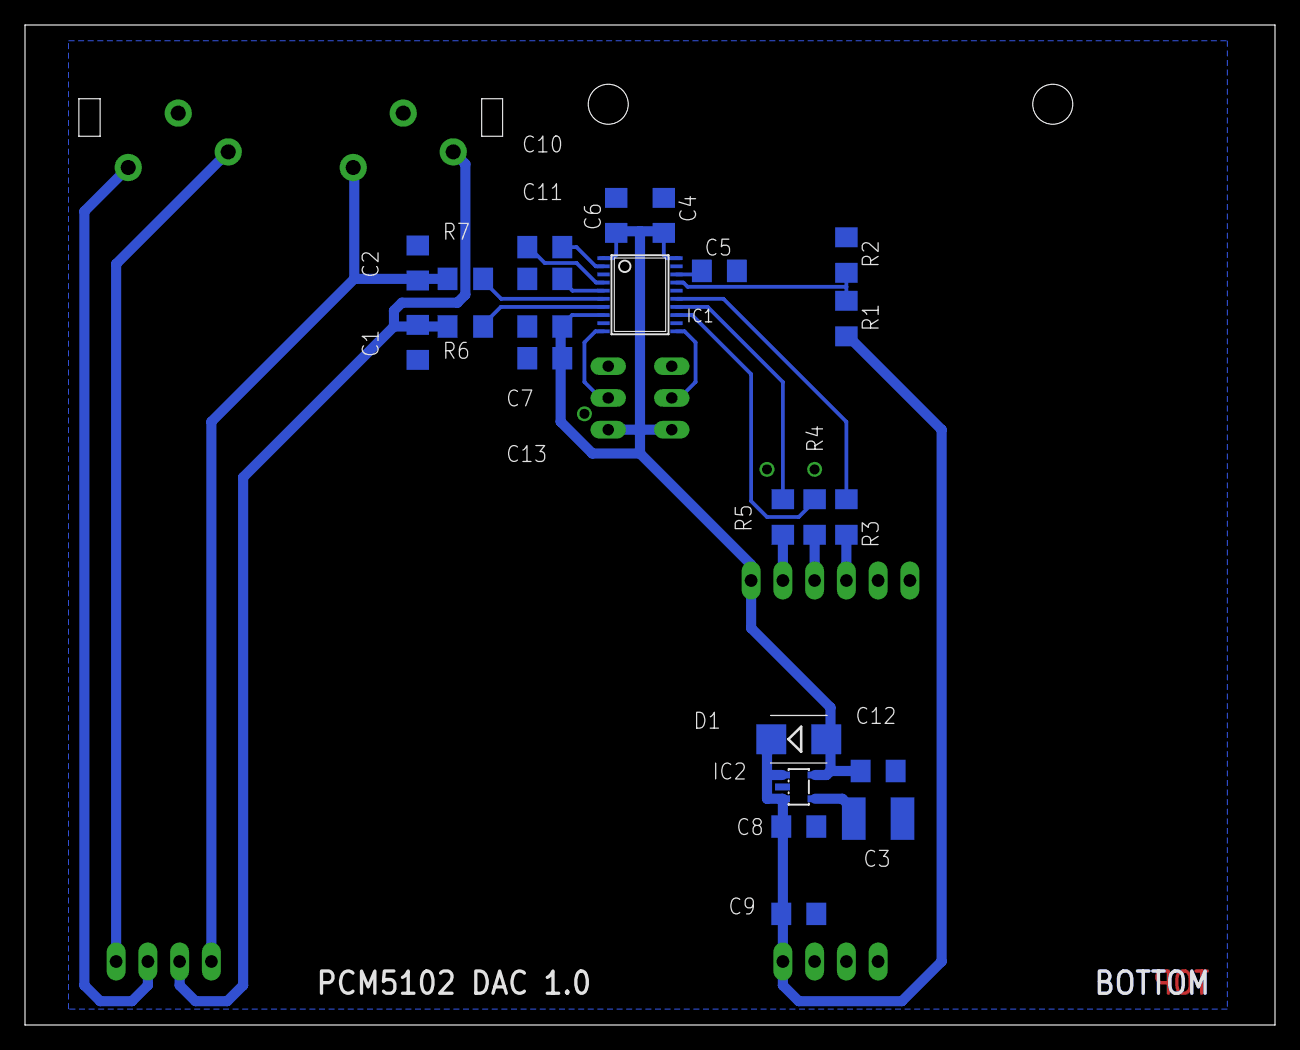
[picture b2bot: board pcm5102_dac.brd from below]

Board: 2 copper layers, 100.0 x 80.0 mm, 31 parts (23 on the bottom side), 23 nets.

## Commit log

2019-11-05 added dac schematic
2019-11-05 added dac pcb design
2019-11-10 added headphone amp pcb design
2019-11-10 added hedphone amp schematic design
2019-11-23 Create about
2019-11-23 Added firmware for interface with software volume control
2019-11-23 inspiring stuff
2019-11-23 Write some taughts about the firmware
2019-11-23 Working interface...yikes :)
    In this photo the interface is working only on DAC outputs,because i need to design a power supply for the amplifier for fully working mode (the dac outputs overrides the amplifier right now).
2019-11-23 ASIO interpreter app
2019-11-24 Added WASAPI plugin for foobar2000 player
2019-11-26 some taughts about files
2019-11-28 dac case format
2019-11-28 Some stuff about USB Audio Class
2019-11-28 More stuff about UAC
2019-11-29 added schematic for power supply
